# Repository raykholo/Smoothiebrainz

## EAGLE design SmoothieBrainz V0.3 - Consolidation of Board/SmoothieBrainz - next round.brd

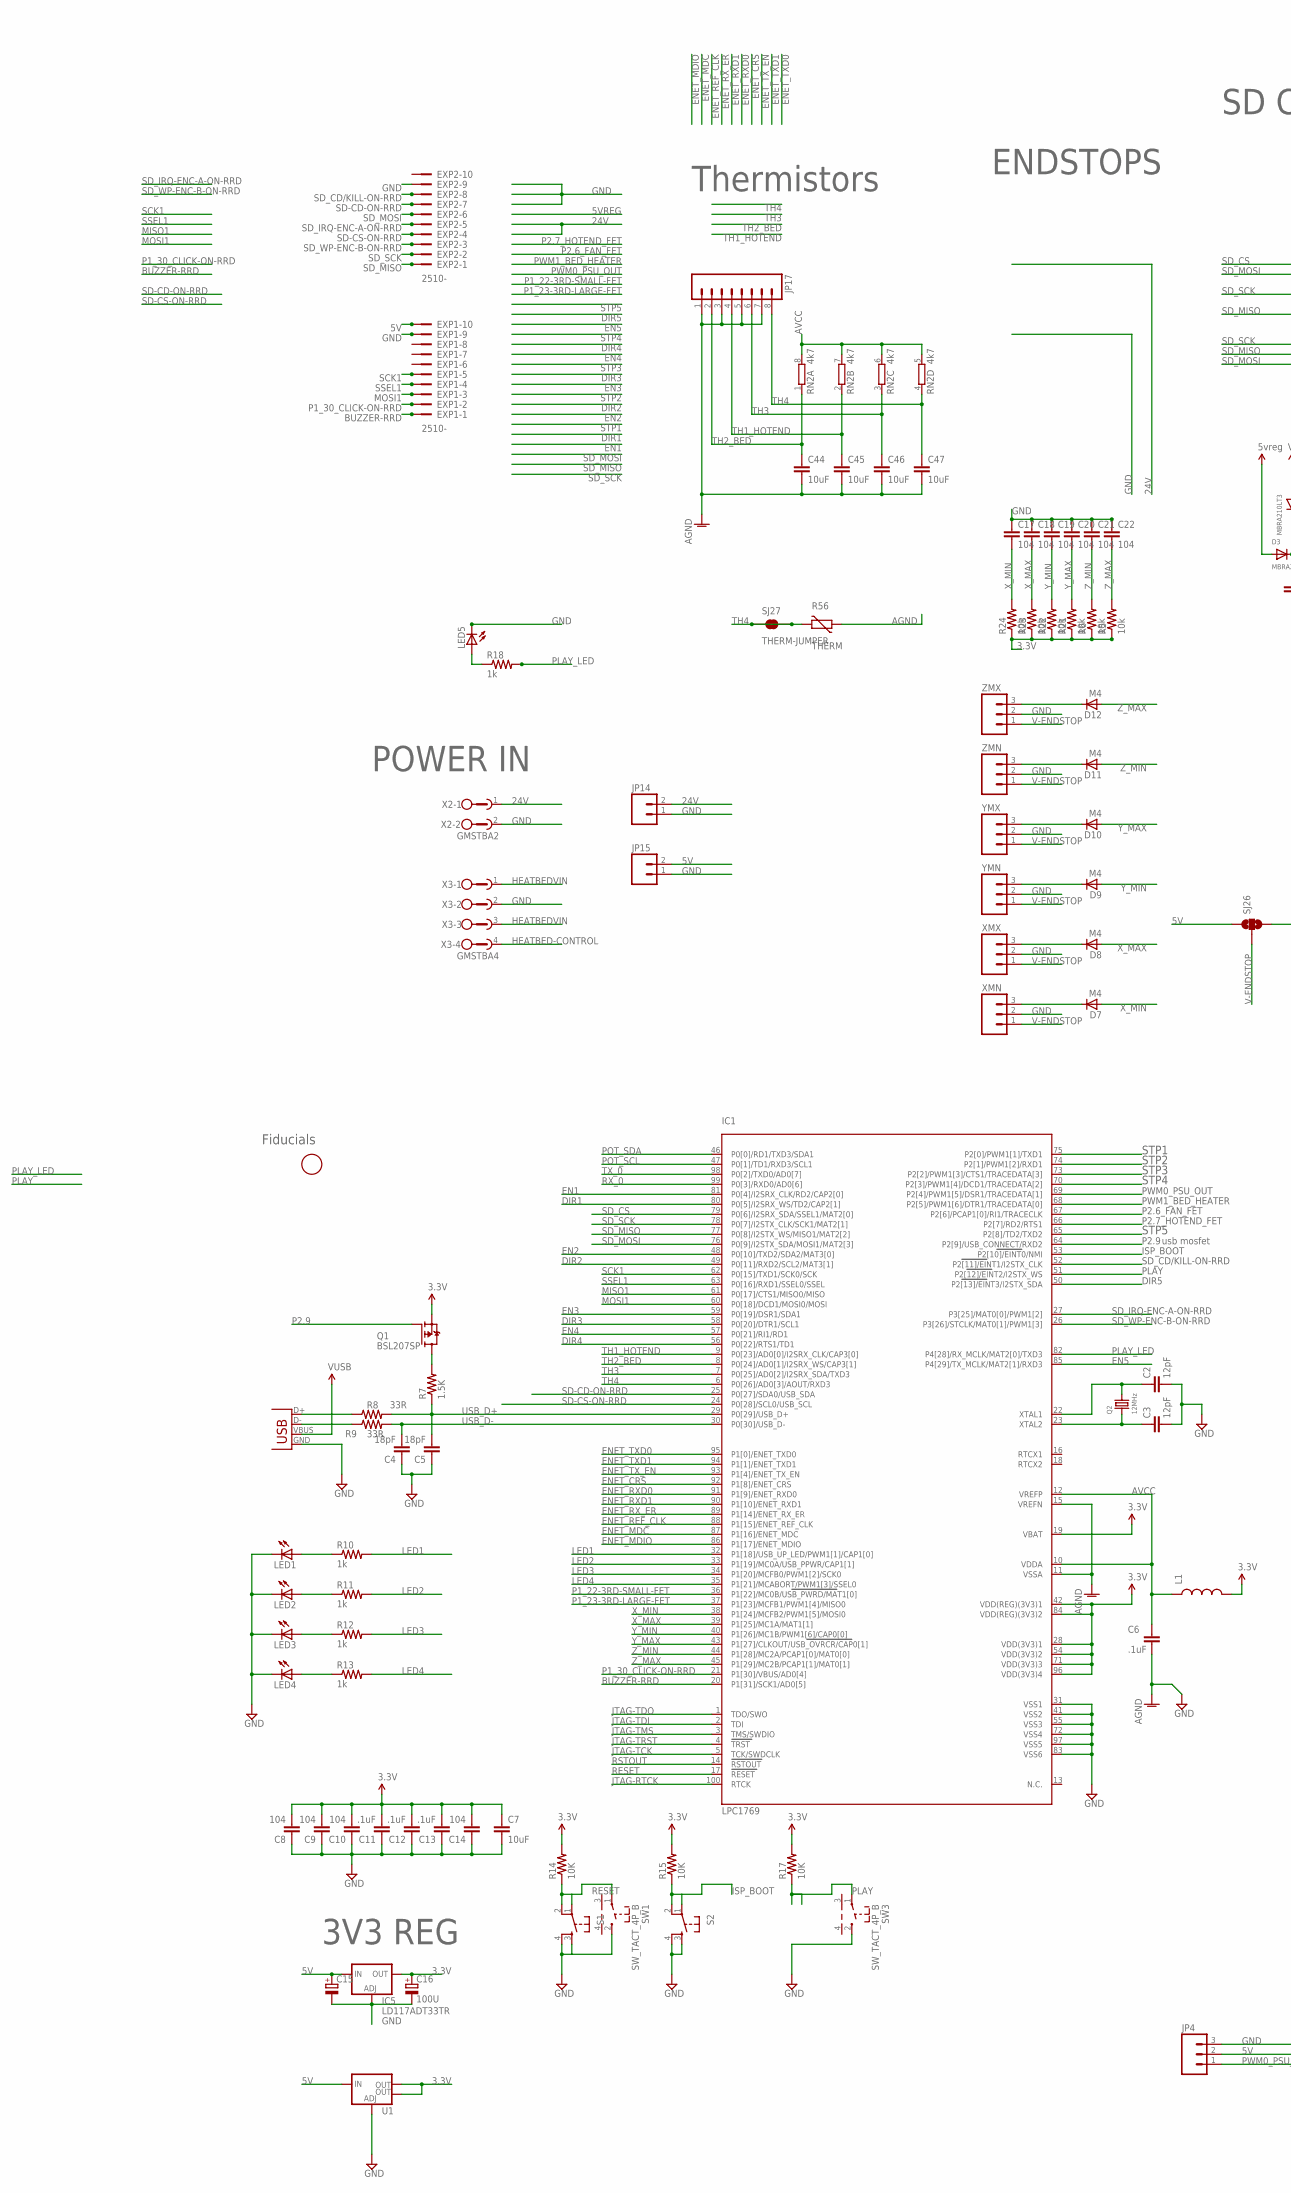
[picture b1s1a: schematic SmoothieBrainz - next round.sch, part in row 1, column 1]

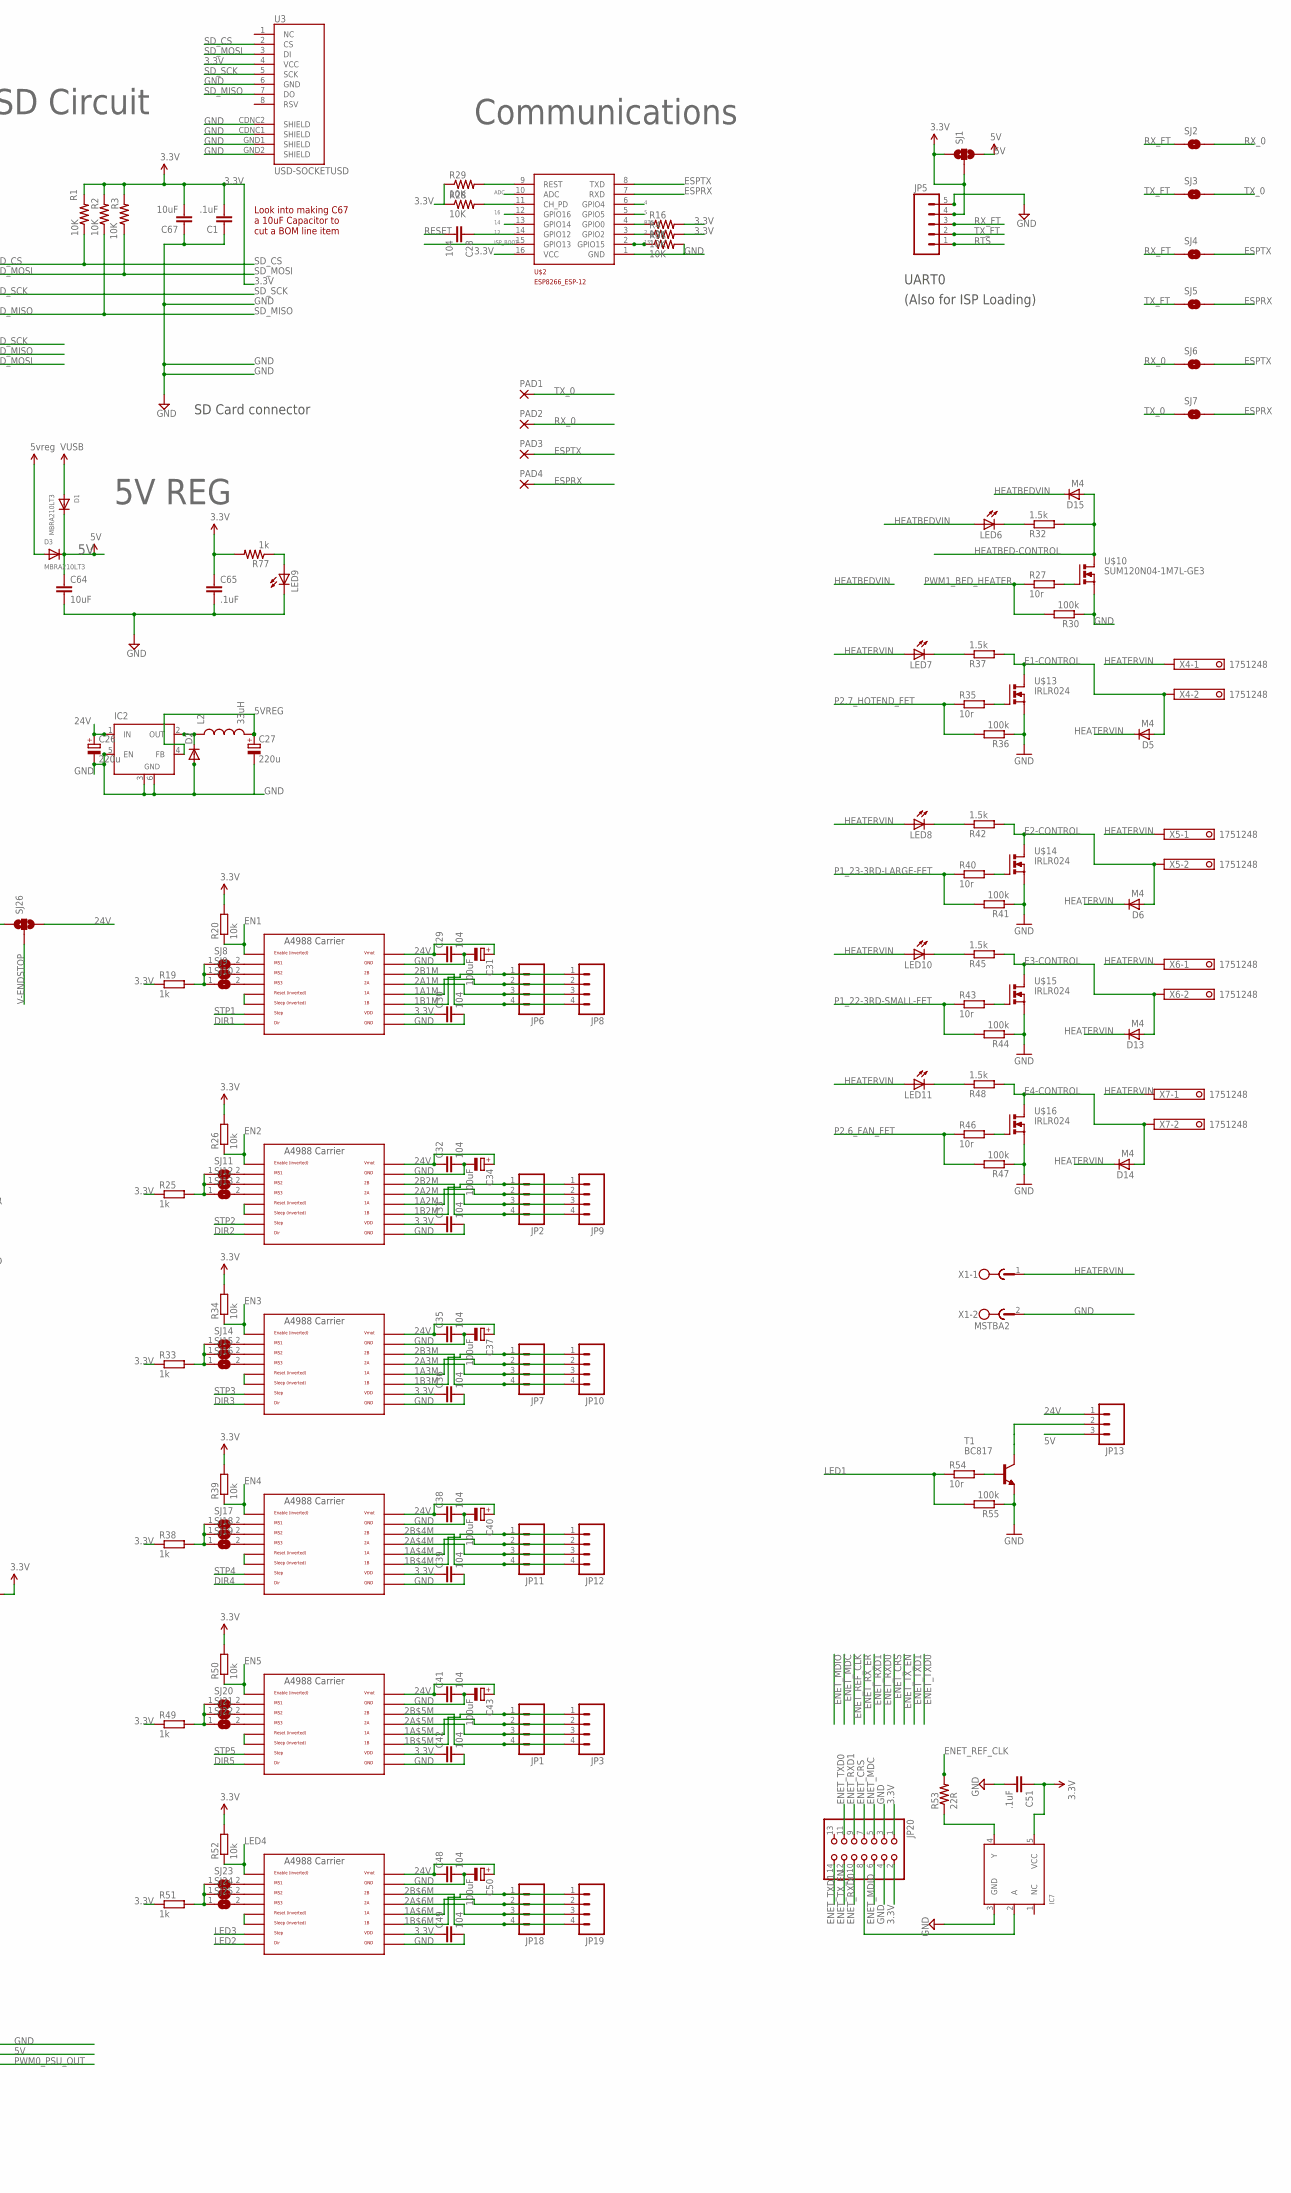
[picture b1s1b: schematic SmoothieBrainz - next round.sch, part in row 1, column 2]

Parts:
C1, C51, C65: .1uF; C0603
C2, C3: 12pF; C0603@1
C4, C5: 18pF; C0603@1
C6, C11, C12, C13: .1uF; C0603@1
C7, C44, C45, C46, C47, C64, C67: 10uF; C0603
C8, C9, C10, C14: 104; C0603@1
C15: CPOL-EUE2.5-7; E2,5-7
C16: 100U; E2,5-7
C17, C18, C19, C20, C21, C22, C28, C29, C30, C32, C33, C35, C36, C38, C39, C41, C42, C48, C49: 104; C0603
C26, C27: 220u; E2,5-7
C31, C34, C37, C40, C43, C50: 100uF; 153CLV-0605
D1, D3: MBRA210LT3; SMADIODE
D2: DIODE-DO-214AC; DO-214AC
D5, D6, D7, D8, D9, D10, D11, D12, D13, D14, D15: M4; SOD87
EXP1, EXP2: 2510-; PAK100/2500-10
IC1: LPC1769; LQFP100
IC2: LM2596S; TO263-5
IC5: LD117ADT33TR; DPACK
IC7: 74LVC1G04; SOT23-5
JP1, JP2, JP6, JP7, JP11, JP18: M04POLAR_LOCK; MOLEX-1X4_LOCK
JP3, JP8, JP9, JP10, JP12, JP19: M04LOCK; 1X04_LOCK
JP4, JP13: M03LOCK; 1X03_LOCK
JP5: M05NO_SILK; 1X05_NO_SILK
JP14, JP15: M02LOCK; 1X02_LOCK
JP17: M08LOCK; 1X08_LOCK
JP20: PINHD-2X7; 2X07
L1: INDUCTOR0603; 0603
L2: 33uH; CDRH125
LED1, LED2, LED3, LED4, LED9: LEDCHIP-LED0805; CHIP-LED0805
LED5: LEDCHIP-LED0603; CHIP-LED0603
LED6, LED7, LED8, LED10, LED11: LEDSML0603; SML0603
PAD1, PAD2, PAD3, PAD4: 1,6/0,9
Q1: BSL207SP; SC74_INFINEON
Q2: 12MHz; CRYSTAL_3.2X2.5
R1, R2, R3, R4, R14, R15, R16, R17, R28, R29, R31: 10K; R0603
R5, R6, R20, R21, R22, R23, R24, R26, R34, R39, R50, R52: 10k; R0603
R7: 1.5K; R0603
R8, R9: 33R; R0603
R10, R11, R12, R13, R18, R19, R25, R33, R38, R49, R51, R77: 1k; R0603
R27, R35, R40, R43, R46, R54: 10r; R0603
R30, R36, R41, R44, R47, R55: 100k; R0603
R32, R37, R42, R45, R48: 1.5k; R0603
R53: 22R; R0603
R56: THERM; CT/CN0603
RN2: 4k7; 0603-ARV
S1, S2: TAC_SWITCHSMD; TACTILE_SWITCH_SMD
SJ1, SJ26: SOLDERJUMPER_2WAYS; SJ_3
SJ2, SJ3, SJ4, SJ5, SJ6, SJ7: SOLDERJUMPERNC; SJ_2S
SJ8, SJ9, SJ10, SJ11, SJ12, SJ13, SJ14, SJ15, SJ16, SJ17, SJ18, SJ19, SJ20, SJ21, SJ22, SJ23, SJ24, SJ25: SJ
SJ27: THERM-JUMPER; SJ_2S-TRACE
SW1, SW3: SW_TACT_4P_B; SW_TACT_STANDARD_RIGHT_ANGLE
T1: BC817; SOT23-BEC
U1: V_REG_LM1117SOT223; SOT223
U3: USD-SOCKETUSD; USD-SOCKET-PP
U$1, U$5, U$6, U$7, U$8, U$9: POLOLU_A4983CARRIER; A4988BREAKOUT
U$2: ESP8266_ESP-12; ESP8266-ESP12
U$10: SUM120N04-1M7L-GE3; D2PACK
U$12: FIDUCIAL; FIDUCIAL_1MM
U$13, U$14, U$15, U$16: IRLR024; D-PAK_TO252AA
X1: MSTBA2
X2: GMSTBA2
X3: GMSTBA4
X4, X5, X6, X7: 1751248
X14: USBPTH; USB-B-PTH
XMN: M03POLAR_LOCK; MOLEX-1X3_LOCK
XMX: M03POLAR_LOCK; MOLEX-1X3_LOCK
YMN: M03POLAR_LOCK; MOLEX-1X3_LOCK
YMX: M03POLAR_LOCK; MOLEX-1X3_LOCK
ZMN: M03POLAR_LOCK; MOLEX-1X3_LOCK
ZMX: M03POLAR_LOCK; MOLEX-1X3_LOCK

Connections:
1A1M: JP6.2, JP8.2, U$1.1A
1A2M: JP2.2, JP9.2, U$5.1A
1A3M: JP7.2, JP10.2, U$6.1A
1A$4M: JP11.2, JP12.2, U$7.1A
1A$5M: JP1.2, JP3.2, U$8.1A
1A$6M: JP18.2, JP19.2, U$9.1A
1B1M: JP6.1, JP8.1, U$1.1B
1B2M: JP2.1, JP9.1, U$5.1B
1B3M: JP7.1, JP10.1, U$6.1B
1B$4M: JP11.1, JP12.1, U$7.1B
1B$5M: JP1.1, JP3.1, U$8.1B
1B$6M: JP18.1, JP19.1, U$9.1B
2: R4.1, U$2.3 (GPIO2)
2A1M: JP6.3, JP8.3, U$1.2A
2A2M: JP2.3, JP9.3, U$5.2A
2A3M: JP7.3, JP10.3, U$6.2A
2A$4M: JP11.3, JP12.3, U$7.2A
2A$5M: JP1.3, JP3.3, U$8.2A
2A$6M: JP18.3, JP19.3, U$9.2A
2B1M: JP6.4, JP8.4, U$1.2B
2B2M: JP2.4, JP9.4, U$5.2B
2B3M: JP7.4, JP10.4, U$6.2B
2B$4M: JP11.4, JP12.4, U$7.2B
2B$5M: JP1.4, JP3.4, U$8.2B
2B$6M: JP18.4, JP19.4, U$9.2B
3.3V: C1.2, C7.1, C8.2, C9.2, C10.2, C11.2, C12.2, C13.2, C14.2, C16.+, C30.1, C33.1, C36.1, C39.1, C42.1, C49.1, C51.1, C65.1, C67.2, IC1.19 (VBAT), IC1.28 (VDD(3V3)1), IC1.42 (VDD(REG)(3V3)1), IC1.54 (VDD(3V3)2), IC1.71 (VDD(3V3)3), IC1.84 (VDD(REG)(3V3)2), IC1.96 (VDD(3V3)4), IC5.4 (OUT), IC7.5 (VCC), JP5.4, JP20.1, JP20.2, L1.2, Q1.4 (S), R1.2, R2.2, R3.2, R4.2, R5.1, R6.1, R14.2, R15.2, R16.2, R17.2, R19.1, R20.2, R21.1, R22.1, R23.1, R24.1, R25.1, R26.2, R28.1, R29.1, R33.1, R34.2, R38.1, R39.2, R49.1, R50.2, R51.1, R52.2, R77.2, SJ1.1, SJ1.2, U1.2 (OUT), U1.4 (OUT), U3.4 (VCC), U$1.VDD, U$2.16 (VCC), U$5.VDD, U$6.VDD, U$7.VDD, U$8.VDD, U$9.VDD
4: U$2.6 (GPIO4)
5: U$2.5 (GPIO5)
5V: C15.+, C64.1, D1.C, D3.C, EXP1.10, IC5.3 (IN), JP4.2, JP13.3, JP15.2, SJ1.3, SJ26.1, U1.3 (IN)
5VREG: C27.+, D3.A, IC2.4 (FB), L2.2
12: C28.1, U$2.14 (GPIO12)
14: U$2.13 (GPIO14)
15: R31.1, U$2.2 (GPIO15)
16: U$2.12 (GPIO16)
24V: C26.+, C29.1, C31.+, C32.1, C34.+, C35.1, C37.+, C38.1, C40.+, C41.1, C43.+, C48.1, C50.+, IC2.1 (IN), JP13.1, JP14.2, SJ26.3, U$1.VMOT, U$5.VMOT, U$6.VMOT, U$7.VMOT, U$8.VMOT, U$9.VMOT, X2.1
ADC: U$2.10 (ADC)
AGND: C6.2, C44.2, C45.2, C46.2, C47.2, IC1.11 (VSSA), IC1.15 (VREFN), JP17.1, JP17.3, JP17.5, JP17.7, R56.1
AVCC: C6.1, IC1.10 (VDDA), IC1.12 (VREFP), L1.1, RN2.5 (2), RN2.6 (2), RN2.7 (2), RN2.8 (2)
BUZZER-RRD: EXP1.1, IC1.20 (P1[31]/SCK1/AD0[5])
DIR1: IC1.80 (P0[5]/I2SRX_WS/TD2/CAP2[1]), U$1.DIR
DIR2: IC1.49 (P0[11]/RXD2/SCL2/MAT3[1]), U$5.DIR
DIR3: IC1.58 (P0[20]/DTR1/SCL1), U$6.DIR
DIR4: IC1.56 (P0[22]/RTS1/TD1), U$7.DIR
DIR5: IC1.50 (P2[13]/EINT3/I2STX_SDA), U$8.DIR
E1-CONTROL: D5.2 (A), R37.2, U$13.4 (D), X4.2
E2-CONTROL: D6.2 (A), R42.2, U$14.4 (D), X5.2
E3-CONTROL: D13.2 (A), R45.2, U$15.4 (D), X6.2
E4-CONTROL: D14.2 (A), R48.2, U$16.4 (D), X7.2
EN1: IC1.81 (P0[4]/I2SRX_CLK/RD2/CAP2[0]), R20.1, U$1.EN
EN2: IC1.48 (P0[10]/TXD2/SDA2/MAT3[0]), R26.1, U$5.EN
EN3: IC1.59 (P0[19]/DSR1/SDA1), R34.1, U$6.EN
EN4: IC1.57 (P0[21]/RI1/RD1), R39.1, U$7.EN
EN5: IC1.85 (P4[29]/TX_MCLK/MAT2[1]/RXD3), R50.1, U$8.EN
ENET_CRS: IC1.92 (P1[8]/ENET_CRS), JP20.7
ENET_MDC: IC1.87 (P1[16]/ENET_MDC), JP20.5
ENET_MDIO: IC1.86 (P1[17]/ENET_MDIO), JP20.6
ENET_REF_CLK: IC1.88 (P1[15]/ENET_REF_CLK), R53.2
ENET_RXD0: IC1.91 (P1[9]/ENET_RXD0), JP20.10
ENET_RXD1: IC1.90 (P1[10]/ENET_RXD1), JP20.9
ENET_RX_ER: IC1.89 (P1[14]/ENET_RX_ER)
ENET_TXD0: IC1.95 (P1[0]/ENET_TXD0), JP20.11
ENET_TXD1: IC1.94 (P1[1]/ENET_TXD1), JP20.14
ENET_TX_EN: IC1.93 (P1[4]/ENET_TX_EN), JP20.12
ESPRX: PAD4.1, SJ5.2, SJ7.2, U$2.7 (RXD)
ESPTX: PAD3.1, SJ4.2, SJ6.2, U$2.8 (TXD)
GND: C1.1, C2.2, C3.2, C4.1, C5.1, C7.2, C8.1, C9.1, C10.1, C11.1, C12.1, C13.1, C14.1, C15.-, C16.-, C17.1, C18.1, C19.1, C20.1, C21.1, C22.1, C26.-, C27.-, C29.2, C30.2, C31.-, C32.2, C33.2, C34.-, C35.2, C36.2, C37.-, C38.2, C39.2, C40.-, C41.2, C42.2, C43.-, C48.2, C49.2, C50.-, C51.2, C64.2, C65.2, C67.1, D2.2 (A), EXP1.9, EXP2.9, IC1.31 (VSS1), IC1.41 (VSS2), IC1.55 (VSS3), IC1.72 (VSS4), IC1.83 (VSS6), IC1.97 (VSS5), IC2.3 (GND), IC2.5 (EN), IC2.6 (GND), IC5.1 (ADJ), IC7.3 (GND), JP4.3, JP5.5, JP14.1, JP15.1, JP20.3, JP20.4, LED1.C, LED2.C, LED3.C, LED4.C, LED5.C, LED9.C, R30.1, R31.2, R36.1, R41.1, R44.1, R47.1, R55.1, S1.3, S1.4, S2.3, S2.4, SW1.2, SW3.2, T1.E, U1.1 (ADJ), U3.6 (GND), U3.CDNC1 (SHIELD), U3.CDNC2 (SHIELD), U3.GND1 (SHIELD), U3.GND2 (SHIELD), U$1.GND, U$1.GND@0 (GND), U$2.1 (GND), U$5.GND, U$5.GND@0 (GND), U$6.GND, U$6.GND@0 (GND), U$7.GND, U$7.GND@0 (GND), U$8.GND, U$8.GND@0 (GND), U$9.GND, U$9.GND@0 (GND), U$10.3 (S), U$13.3 (S), U$14.3 (S), U$15.3 (S), U$16.3 (S), X1.2, X2.2, X3.2, X14.GND, XMN.2, XMX.2, YMN.2, YMX.2, ZMN.2, ZMX.2
HEATBED-CONTROL: D15.2 (A), R32.2, U$10.2 (D), X3.4
HEATBEDVIN: D15.1 (C), LED6.A, X3.1, X3.3
HEATERVIN: D5.1 (C), D6.1 (C), D13.1 (C), D14.1 (C), LED7.A, LED8.A, LED10.A, LED11.A, X1.1, X4.1, X5.1, X6.1, X7.1
ISP_BOOT: IC1.53 (P2[10]/EINT0/NMI), R15.1, S2.1, S2.2, U$2.15 (GPIO13)
JTAG-RTCK: IC1.100 (RTCK)
JTAG-TCK: IC1.5 (TCK/SWDCLK)
JTAG-TDI: IC1.2 (TDI)
JTAG-TDO: IC1.1 (TDO/SWO)
JTAG-TMS: IC1.3 (TMS/SWDIO)
JTAG-TRST: IC1.4 (TRST)
LED1: IC1.32 (P1[18]/USB_UP_LED/PWM1[1]/CAP1[0]), R10.2, R54.1, R55.2
LED2: IC1.33 (P1[19]/MC0A/USB_PPWR/CAP1[1]), R11.2, U$9.DIR
LED3: IC1.34 (P1[20]/MCFB0/PWM1[2]/SCK0), R12.2, U$9.STEP
LED4: IC1.35 (P1[21]/MCABORT/PWM1[3]/SSEL0), R13.2, R52.1, U$9.EN
MISO1: IC1.61 (P0[17]/CTS1/MISO0/MISO)
MOSI1: EXP1.3, IC1.60 (P0[18]/DCD1/MOSI0/MOSI)
unnamed: C2.1, IC1.22 (XTAL1), Q2.2
unnamed: C3.1, IC1.23 (XTAL2), Q2.1
unnamed: LED5.A, R18.1
unnamed: D11.1 (C), ZMN.3
unnamed: D10.1 (C), YMX.3
unnamed: SJ8.2, U$1.MS1
unnamed: D9.1 (C), YMN.3
unnamed: SJ9.2, U$1.MS2
unnamed: D2.1 (C), IC2.2 (OUT), L2.1
unnamed: SJ10.2, U$1.MS3
unnamed: D8.1 (C), XMX.3
unnamed: U$5.RST, U$5.SLP (SLEEP)
unnamed: D7.1 (C), XMN.3
unnamed: R25.2, SJ11.1, SJ12.1, SJ13.1
unnamed: SJ11.2, U$5.MS1
unnamed: D12.1 (C), ZMX.3
unnamed: SJ12.2, U$5.MS2
unnamed: R28.2, U$2.11 (CH_PD)
unnamed: SJ13.2, U$5.MS3
unnamed: R27.2, U$10.1 (G)
unnamed: LED6.C, R32.1
unnamed: U$6.RST, U$6.SLP (SLEEP)
unnamed: R33.2, SJ14.1, SJ15.1, SJ16.1
unnamed: SJ14.2, U$6.MS1
unnamed: SJ15.2, U$6.MS2
unnamed: SJ16.2, U$6.MS3
unnamed: R35.2, U$13.1 (G)
unnamed: R19.2, SJ8.1, SJ9.1, SJ10.1
unnamed: LED7.C, R37.1
unnamed: U$7.RST, U$7.SLP (SLEEP)
unnamed: R38.2, SJ17.1, SJ18.1, SJ19.1
unnamed: SJ17.2, U$7.MS1
unnamed: SJ18.2, U$7.MS2
unnamed: U$1.RST, U$1.SLP (SLEEP)
unnamed: SJ19.2, U$7.MS3
unnamed: R40.2, U$14.1 (G)
unnamed: LED8.C, R42.1
unnamed: R43.2, U$15.1 (G)
unnamed: LED10.C, R45.1
unnamed: R46.2, U$16.1 (G)
unnamed: LED11.C, R48.1
unnamed: U$8.RST, U$8.SLP (SLEEP)
unnamed: R49.2, SJ20.1, SJ21.1, SJ22.1
unnamed: SJ20.2, U$8.MS1
unnamed: SJ21.2, U$8.MS2
unnamed: SJ22.2, U$8.MS3
unnamed: U$9.RST, U$9.SLP (SLEEP)
unnamed: R51.2, SJ23.1, SJ24.1, SJ25.1
unnamed: SJ23.2, U$9.MS1
unnamed: Q1.1 (D), Q1.2 (D), Q1.5 (D), Q1.6 (D), R7.2
unnamed: SJ24.2, U$9.MS2
unnamed: SJ25.2, U$9.MS3
unnamed: R54.2, T1.B
unnamed: JP13.2, T1.C
unnamed: R8.1, X14.D+
unnamed: R9.1, X14.D-
unnamed: IC7.2 (A), JP20.8
unnamed: IC7.4 (Y), R53.1
unnamed: LED9.A, R77.1
unnamed: LED4.A, R13.1
unnamed: LED3.A, R12.1
unnamed: LED2.A, R11.1
unnamed: LED1.A, R10.1
P1_22-3RD-SMALL-FET: IC1.36 (P1[22]/MC0B/USB_PWRD/MAT1[0]), R43.1, R44.2
P1_23-3RD-LARGE-FET: IC1.37 (P1[23]/MCFB1/PWM1[4]/MISO0), R40.1, R41.2
P1_30_CLICK-ON-RRD: EXP1.2, IC1.21 (P1[30]/VBUS/AD0[4])
P2.6_FAN_FET: IC1.67 (P2[6]/PCAP1[0]/RI1/TRACECLK), R46.1, R47.2
P2.7_HOTEND_FET: IC1.66 (P2[7]/RD2/RTS1), R35.1, R36.2
P2.9: IC1.64 (P2[9]/USB_CONNECT/RXD2), Q1.3 (G)
PLAY: IC1.51 (P2[12]/EINT2/I2STX_WS), R17.1, SW3.1
PLAY_LED: IC1.82 (P4[28]/RX_MCLK/MAT2[0]/TXD3), R18.2
POT_SCL: IC1.47 (P0[1]/TD1/RXD3/SCL1)
POT_SDA: IC1.46 (P0[0]/RD1/TXD3/SDA1)
PWM0_PSU_OUT: IC1.69 (P2[4]/PWM1[5]/DSR1/TRACEDATA[1]), JP4.1
PWM1_BED_HEATER: IC1.68 (P2[5]/PWM1[6]/DTR1/TRACEDATA[0]), R27.1, R30.2
RESET: C28.2, IC1.17 (RESET), R14.1, S1.1, S1.2, SW1.1
RESET1: R29.2, U$2.9 (REST)
RSTOUT: IC1.14 (RSTOUT)
RTS: JP5.1, R16.1, U$2.4 (GPIO0)
RX_0: IC1.99 (P0[3]/RXD0/AD0[6]), PAD2.1, SJ2.2, SJ6.1
RX_FT: JP5.3, SJ2.1, SJ4.1
SCK1: EXP1.5, IC1.62 (P0[15]/TXD1/SCK0/SCK)
SD-CD-ON-RRD: EXP2.7, IC1.25 (P0[27]/SDA0/USB_SDA)
SD-CS-ON-RRD: EXP2.4, IC1.24 (P0[28]/SCL0/USB_SCL)
SD_CD/KILL-ON-RRD: EXP2.8, IC1.52 (P2[11]/EINT1/I2STX_CLK)
SD_CS: IC1.79 (P0[6]/I2SRX_SDA/SSEL1/MAT2[0]), R1.1, U3.2 (CS)
SD_IRQ-ENC-A-ON-RRD: EXP2.5, IC1.27 (P3[25]/MAT0[0]/PWM1[2])
SD_MISO: EXP2.1, IC1.77 (P0[8]/I2STX_WS/MISO1/MAT2[2]), R2.1, U3.7 (DO)
SD_MOSI: EXP2.6, IC1.76 (P0[9]/I2STX_SDA/MOSI1/MAT2[3]), R3.1, U3.3 (DI)
SD_SCK: EXP2.2, IC1.78 (P0[7]/I2STX_CLK/SCK1/MAT2[1]), U3.5 (SCK)
SD_WP-ENC-B-ON-RRD: EXP2.3, IC1.26 (P3[26]/STCLK/MAT0[1]/PWM1[3])
SSEL1: EXP1.4, IC1.63 (P0[16]/RXD1/SSEL0/SSEL)
STP1: IC1.75 (P2[0]/PWM1[1]/TXD1), U$1.STEP
STP2: IC1.74 (P2[1]/PWM1[2]/RXD1), U$5.STEP
STP3: IC1.73 (P2[2]/PWM1[3]/CTS1/TRACEDATA[3]), U$6.STEP
STP4: IC1.70 (P2[3]/PWM1[4]/DCD1/TRACEDATA[2]), U$7.STEP
STP5: IC1.65 (P2[8]/TD2/TXD2), U$8.STEP
TH1_HOTEND: C45.1, IC1.9 (P0[23]/AD0[0]/I2SRX_CLK/CAP3[0]), JP17.4, RN2.2 (1)
TH2_BED: C44.1, IC1.8 (P0[24]/AD0[1]/I2SRX_WS/CAP3[1]), JP17.2, RN2.1
TH3: C46.1, IC1.7 (P0[25]/AD0[2]/I2SRX_SDA/TXD3), JP17.6, RN2.3 (1)
TH4: C47.1, IC1.6 (P0[26]/AD0[3]/AOUT/RXD3), JP17.8, R56.2, RN2.4 (1), SJ27.1, SJ27.2
TX_0: IC1.98 (P0[2]/TXD0/AD0[7]), PAD1.1, SJ3.2, SJ7.1
TX_FT: JP5.2, SJ3.1, SJ5.1
USB_D+: C5.2, IC1.29 (P0[29]/USB_D+), R7.1, R8.2
USB_D-: C4.2, IC1.30 (P0[30]/USB_D-), R9.2
V-ENDSTOP: SJ26.2, XMN.1, XMX.1, YMN.1, YMX.1, ZMN.1, ZMX.1
VUSB: D1.A, X14.VBUS
X_MAX: C18.2, D8.2 (A), IC1.39 (P1[25]/MC1A/MAT1[1]), R23.2
X_MIN: C17.2, D7.2 (A), IC1.38 (P1[24]/MCFB2/PWM1[5]/MOSI0), R24.2
Y_MAX: C20.2, D10.2 (A), IC1.43 (P1[27]/CLKOUT/USB_OVRCR/CAP0[1]), R21.2
Y_MIN: C19.2, D9.2 (A), IC1.40 (P1[26]/MC1B/PWM1[6]/CAP0[0]), R22.2
Z_MAX: C22.2, D12.2 (A), IC1.45 (P1[29]/MC2B/PCAP1[1]/MAT0[1]), R5.2
Z_MIN: C21.2, D11.2 (A), IC1.44 (P1[28]/MC2A/PCAP1[0]/MAT0[0]), R6.2

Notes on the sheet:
SD Card connector
UART0
(Also for ISP Loading)
usb mosfet
5V REG
SD Circuit
Communications
3V3 REG
ENDSTOPS
Look into making C67 a 10uF Capacitor to cut a BOM line item
Thermistors
Fiducials
POWER IN

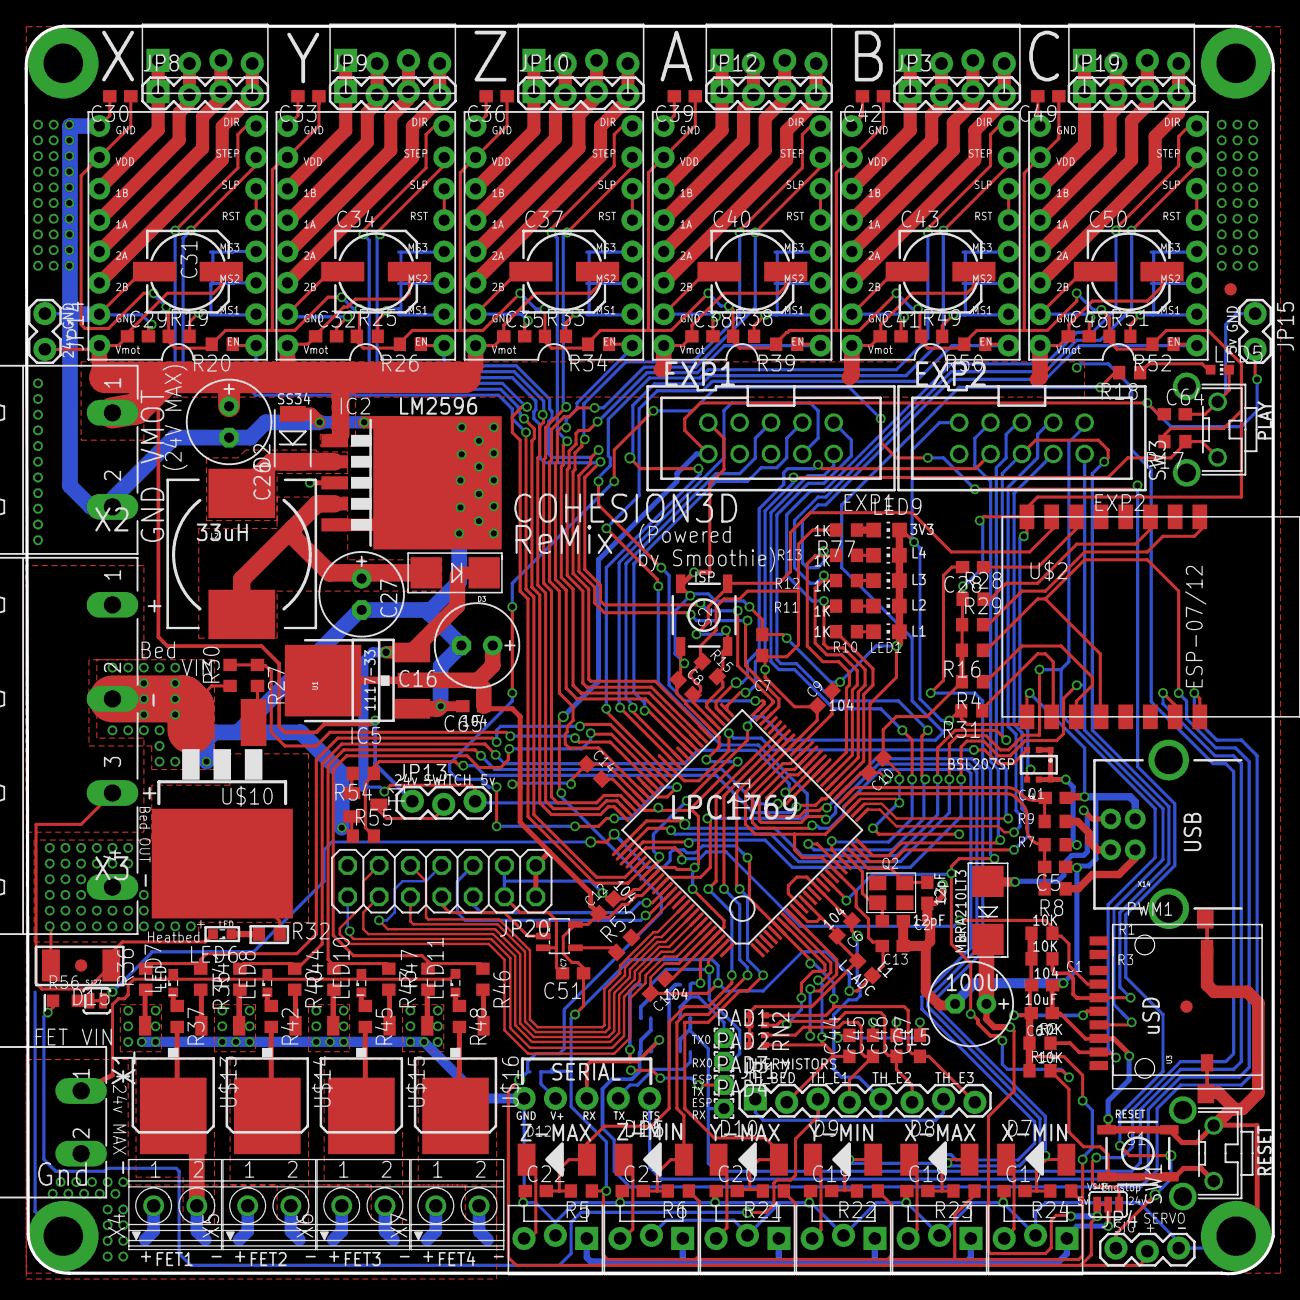
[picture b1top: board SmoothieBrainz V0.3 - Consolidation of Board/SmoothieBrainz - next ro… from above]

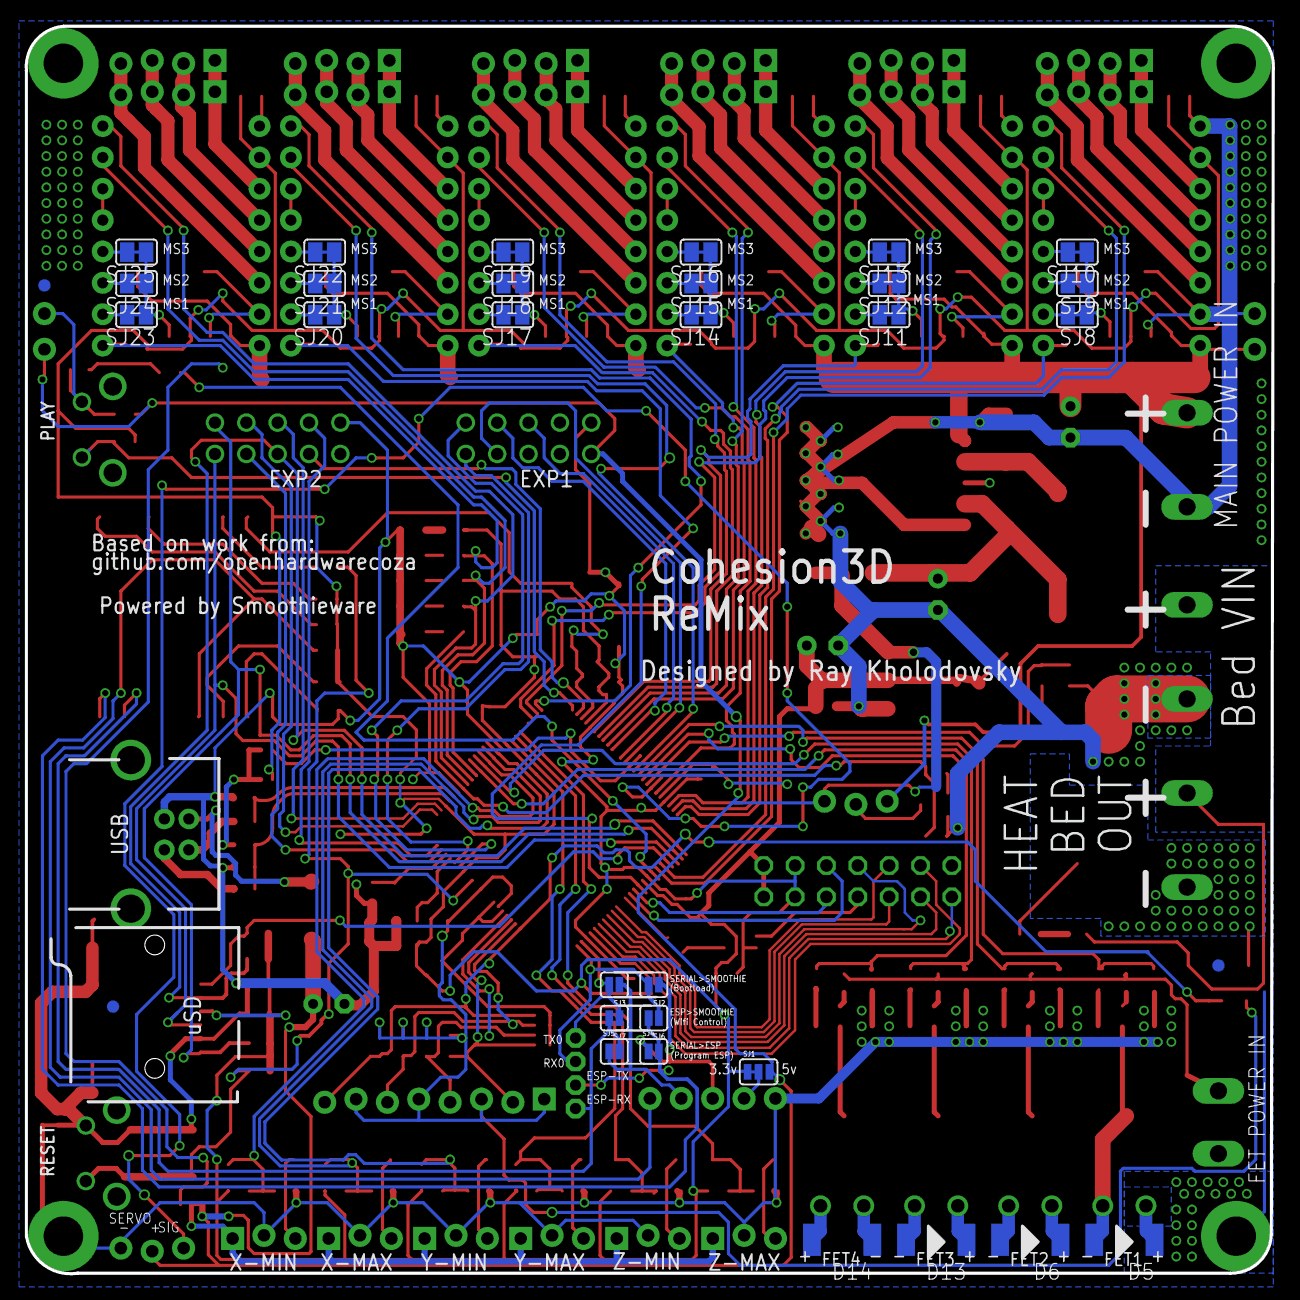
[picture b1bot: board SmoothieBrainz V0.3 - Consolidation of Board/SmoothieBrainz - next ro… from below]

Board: 2 copper layers, 101.0 x 101.0 mm, 233 parts (32 on the bottom side), 179 nets.

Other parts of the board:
U$11, U$17, U$18, U$19, U$20: FIDUCIAL; FIDUCIAL_1MM

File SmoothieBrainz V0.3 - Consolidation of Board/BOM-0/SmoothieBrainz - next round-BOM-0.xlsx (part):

Part | Value | Device | Package | Description | MF | MPN | OC_FARNELL | OC_NEWARK | PROD_ID
C1 | .1uF | C-EUC0603 | C0603 | CAPACITOR, European symbol
C2 | 12pF | C-EUC0603 | C0603@1 | CAPACITOR, European symbol
C3 | 12pF | C-EUC0603 | C0603@1 | CAPACITOR, European symbol
C4 | 18pF | C-EUC0603 | C0603@1 | CAPACITOR, European symbol
C5 | 18pF | C-EUC0603 | C0603@1 | CAPACITOR, European symbol
C6 | .1uF | C-EUC0603 | C0603@1 | CAPACITOR, European symbol
C7 | 10uF | C-EUC0603 | C0603 | CAPACITOR, European symbol
C8 | .1uF | C-EUC0603 | C0603@1 | CAPACITOR, European symbol
C9 | .1uF | C-EUC0603 | C0603@1 | CAPACITOR, European symbol
C10 | .1uF | C-EUC0603 | C0603@1 | CAPACITOR, European symbol
C11 | .1uF | C-EUC0603 | C0603@1 | CAPACITOR, European symbol
C12 | .1uF | C-EUC0603 | C0603@1 | CAPACITOR, European symbol
C13 | .1uF | C-EUC0603 | C0603@1 | CAPACITOR, European symbol
C14 | .1uF | C-EUC0603 | C0603@1 | CAPACITOR, European symbol
C15 |  | CPOL-EUE2.5-7 | E2,5-7 | POLARIZED CAPACITOR, European symbol
C16 | 100U | CPOL-EUE2.5-7 | E2,5-7 | POLARIZED CAPACITOR, European symbol
C17 | 104 | C-EUC0603 | C0603 | CAPACITOR, European symbol
C18 | 104 | C-EUC0603 | C0603 | CAPACITOR, European symbol
C19 | 104 | C-EUC0603 | C0603 | CAPACITOR, European symbol
C20 | 104 | C-EUC0603 | C0603 | CAPACITOR, European symbol
C21 | 104 | C-EUC0603 | C0603 | CAPACITOR, European symbol
C22 | 104 | C-EUC0603 | C0603 | CAPACITOR, European symbol
C26 | 220u | CPOL-EUE2.5-7 | E2,5-7 | POLARIZED CAPACITOR, European symbol
C27 | 220u | CPOL-EUE2.5-7 | E2,5-7 | POLARIZED CAPACITOR, European symbol
C28 | 104 | C-EUC0603 | C0603 | CAPACITOR, European symbol
C29 | 104 | C-EUC0603 | C0603 | CAPACITOR, European symbol
C30 | 104 | C-EUC0603 | C0603 | CAPACITOR, European symbol
C31 | 100uF | CPOL-EU153CLV-0605 | 153CLV-0605 | POLARIZED CAPACITOR, European symbol
C32 | 104 | C-EUC0603 | C0603 | CAPACITOR, European symbol
C33 | 104 | C-EUC0603 | C0603 | CAPACITOR, European symbol
C34 | 100uF | CPOL-EU153CLV-0605 | 153CLV-0605 | POLARIZED CAPACITOR, European symbol
C35 | 104 | C-EUC0603 | C0603 | CAPACITOR, European symbol
C36 | 104 | C-EUC0603 | C0603 | CAPACITOR, European symbol
C37 | 100uF | CPOL-EU153CLV-0605 | 153CLV-0605 | POLARIZED CAPACITOR, European symbol
C38 | 104 | C-EUC0603 | C0603 | CAPACITOR, European symbol
C39 | 104 | C-EUC0603 | C0603 | CAPACITOR, European symbol
C40 | 100uF | CPOL-EU153CLV-0605 | 153CLV-0605 | POLARIZED CAPACITOR, European symbol
C41 | 104 | C-EUC0603 | C0603 | CAPACITOR, European symbol
C42 | 104 | C-EUC0603 | C0603 | CAPACITOR, European symbol
C43 | 100uF | CPOL-EU153CLV-0605 | 153CLV-0605 | POLARIZED CAPACITOR, European symbol
C44 | 10uF | C-EUC0603 | C0603 | CAPACITOR, European symbol
C45 | 10uF | C-EUC0603 | C0603 | CAPACITOR, European symbol
C46 | 10uF | C-EUC0603 | C0603 | CAPACITOR, European symbol
C47 | 10uF | C-EUC0603 | C0603 | CAPACITOR, European symbol
C48 | 104 | C-EUC0603 | C0603 | CAPACITOR, European symbol
C49 | 104 | C-EUC0603 | C0603 | CAPACITOR, European symbol
C50 | 100uF | CPOL-EU153CLV-0605 | 153CLV-0605 | POLARIZED CAPACITOR, European symbol
C51 | .1uF | C-EUC0603 | C0603 | CAPACITOR, European symbol
C64 | 10uF | C-EUC0603 | C0603 | CAPACITOR, European symbol
C65 | .1uF | C-EUC0603 | C0603 | CAPACITOR, European symbol
C67 | 10uF | C-EUC0603 | C0603 | CAPACITOR, European symbol
D1 | MBRA210LT3 | DIODESMA | SMADIODE | Diode
D2 |  | DIODE-DO-214AC | DO-214AC | Various Diode Packages
D3 | MBRA210LT3 | DIODESMA | SMADIODE | Diode
D5 | M4 | D-SOD-87 | SOD87 | DIODE
D6 | M4 | D-SOD-87 | SOD87 | DIODE
D7 | M4 | D-SOD-87 | SOD87 | DIODE
D8 | M4 | D-SOD-87 | SOD87 | DIODE
D9 | M4 | D-SOD-87 | SOD87 | DIODE
D10 | M4 | D-SOD-87 | SOD87 | DIODE
D11 | M4 | D-SOD-87 | SOD87 | DIODE
D12 | M4 | D-SOD-87 | SOD87 | DIODE
D13 | M4 | D-SOD-87 | SOD87 | DIODE
D14 | M4 | D-SOD-87 | SOD87 | DIODE
D15 | M4 | D-SOD-87 | SOD87 | DIODE
EXP1 | -2510 | -2510 | PAK100/2500-10 | 3M (TM) Pak 100 4-Wall Header | 3M | 2510-6002UB | 9838244 | 46F4725
EXP2 | -2510 | -2510 | PAK100/2500-10 | 3M (TM) Pak 100 4-Wall Header | 3M | 2510-6002UB | 9838244 | 46F4725
IC1 | LPC1769 | LPC1768 | LQFP100 | LPC1768 100 MHz 32-bit ARM Cortex-M3 based microcontroller featuring a high lev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
IC2 |  | LM2596S | TO263-5 | STEP-DOWN VOLTAGE REGULATOR
IC5 | LD117ADT33TR | LD117ADT33TR | DPACK | Low drop fixed and adjustable positive voltage regulators 1 A
IC7 |  | 74LVC1G04 | SOT23-5 | 74LVC1G04 - Single Inverter Gate
JP1 |  | M04POLAR_LOCK | MOLEX-1X4_LOCK | Header 4
JP2 |  | M04POLAR_LOCK | MOLEX-1X4_LOCK | Header 4
JP3 |  | M04LOCK | 1X04_LOCK | Header 4
JP5 |  | M05NO_SILK | 1X05_NO_SILK | Header 5
JP6 |  | M04POLAR_LOCK | MOLEX-1X4_LOCK | Header 4
JP7 |  | M04POLAR_LOCK | MOLEX-1X4_LOCK | Header 4
JP8 |  | M04LOCK | 1X04_LOCK | Header 4
JP9 |  | M04LOCK | 1X04_LOCK | Header 4
JP10 |  | M04LOCK | 1X04_LOCK | Header 4
JP11 |  | M04POLAR_LOCK | MOLEX-1X4_LOCK | Header 4
JP12 |  | M04LOCK | 1X04_LOCK | Header 4
JP13 |  | M03LOCK | 1X03_LOCK | Header 3
JP17 |  | M08LOCK | 1X08_LOCK | Header 8
JP18 |  | M04POLAR_LOCK | MOLEX-1X4_LOCK | Header 4
JP19 |  | M04LOCK | 1X04_LOCK | Header 4
JP20 |  | PINHD-2X7 | 2X07 | PIN HEADER
L1 |  | INDUCTOR0603 | 603 | Inductors
L2 | 33uH | INDUCTORPWR | CDRH125 | Inductors
LED1 |  | LEDCHIP-LED0805 | CHIP-LED0805 | LED
LED2 |  | LEDCHIP-LED0805 | CHIP-LED0805 | LED
LED3 |  | LEDCHIP-LED0805 | CHIP-LED0805 | LED
LED4 |  | LEDCHIP-LED0805 | CHIP-LED0805 | LED
LED5 |  | LEDCHIP-LED0805 | CHIP-LED0805 | LED
LED6 |  | LEDSML0805 | SML0805 | LED
LED7 |  | LEDSML0805 | SML0805 | LED
LED8 |  | LEDSML0805 | SML0805 | LED
LED9 |  | LEDCHIP-LED0805 | CHIP-LED0805 | LED
LED10 |  | LEDSML0805 | SML0805 | LED
LED11 |  | LEDSML0805 | SML0805 | LED
Q1 | BSL207SP | BSL207SP | SC74_INFINEON | OptiMOS(R)-P Small-Signal-Transistor P-Channel, Enhancement mode, Super Logic L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
Q2 | 12MHz | CRYSTALTHIN | CRYSTAL_3.2X2.5 | Crystals
R1 | 10K | R-US_R0603 | R0603 | RESISTOR, American symbol
R2 | 10K | R-US_R0603 | R0603 | RESISTOR, American symbol
R3 | 10K | R-US_R0603 | R0603 | RESISTOR, American symbol
R4 | 10K | R-US_R0603 | R0603 | RESISTOR, American symbol
R5 | 10k | R-US_R0603 | R0603 | RESISTOR, American symbol
R6 | 10k | R-US_R0603 | R0603 | RESISTOR, American symbol
R7 | 1.5K | R-US_R0603 | R0603 | RESISTOR, American symbol
R8 | 33R | R-US_R0603 | R0603 | RESISTOR, American symbol
R9 | 33R | R-US_R0603 | R0603 | RESISTOR, American symbol
R10 | 1k | R-US_R0603 | R0603 | RESISTOR, American symbol
R11 | 1k | R-US_R0603 | R0603 | RESISTOR, American symbol
R12 | 1k | R-US_R0603 | R0603 | RESISTOR, American symbol
R13 | 1k | R-US_R0603 | R0603 | RESISTOR, American symbol
R14 | 10K | R-US_R0603 | R0603 | RESISTOR, American symbol
R15 | 10K | R-US_R0603 | R0603 | RESISTOR, American symbol
R16 | 10K | R-US_R0603 | R0603 | RESISTOR, American symbol
R17 | 10K | R-US_R0603 | R0603 | RESISTOR, American symbol
R18 | 1k | R-US_R0603 | R0603 | RESISTOR, American symbol
R19 | 1k | R-EU_R0603 | R0603 | RESISTOR, European symbol
R20 | 10k | R-EU_R0603 | R0603 | RESISTOR, European symbol
R21 | 10k | R-US_R0603 | R0603 | RESISTOR, American symbol
R22 | 10k | R-US_R0603 | R0603 | RESISTOR, American symbol
R23 | 10k | R-US_R0603 | R0603 | RESISTOR, American symbol
R24 | 10k | R-US_R0603 | R0603 | RESISTOR, American symbol
R25 | 1k | R-EU_R0603 | R0603 | RESISTOR, European symbol
R26 | 10k | R-EU_R0603 | R0603 | RESISTOR, European symbol
R27 | 10r | R-EU_R0603 | R0603 | RESISTOR, European symbol
R28 | 10K | R-US_R0603 | R0603 | RESISTOR, American symbol
R29 | 10K | R-US_R0603 | R0603 | RESISTOR, American symbol
R30 | 100k | R-EU_R0603 | R0603 | RESISTOR, European symbol
R31 | 10K | R-US_R0603 | R0603 | RESISTOR, American symbol
R32 | 1.5k | R-EU_R0603 | R0603 | RESISTOR, European symbol
R33 | 1k | R-EU_R0603 | R0603 | RESISTOR, European symbol
R34 | 10k | R-EU_R0603 | R0603 | RESISTOR, European symbol
R35 | 10r | R-EU_R0603 | R0603 | RESISTOR, European symbol
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

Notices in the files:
parts and their libraries:
SparkFun-Capacitors: Licensing: Creative Commons ShareAlike 4.0 International - https://creativecommons.org/licenses/by-sa/4.0
SparkFun-Passives: Licensing: CC v3.0 Share-Alike You are welcome to use this library for commercial purposes.
